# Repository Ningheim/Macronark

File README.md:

# Macronark, a HXH inspired macropad
A macropad inspired by Shalnark's ability in a popular manga called Hunter X Hunter by Yoshihiro Togashi

The "Macronark" is a 12 key macropad with RGB backlit keys. It uses QMK firmware and is upgradable with a 6-pin JST port on the back of the PCB.

## Features:
- Full PLA Shalnark inspired case
- 12 blank DSA keys
- 12 SK6812 MINI-E LEDs for backlighting

## CAD Model:
Everything is fitted together with 6 M3 bolts and heatset inserts. The PCB sits in flush with the case but there is 1 M3 screw hole if you'd like to secure it to your own case.

It's in 2 parts, 1 part for the body and another for the cover.

Made in Onshape
At a later time a seperate PCB will be used to fill the top portion of the case. More RGB LEDs will be used to light up the eye cutouts and a OLED screen will go inside the mouth just as the series depicts it.

## PCB:
The PCB was made in KiCAD, The silkscreen was imported from a Figma image.

#### Schematic

#### PCB

# Finished Product
Once you've printed everything and inserted/soldered all of the components, the result should look like this! (With keycaps of your choice of course 😅)

## Firmware Overview:
This hackpad uses [QMK](https://qmk.fm/) firmware.
- To turn on/off the RGB backlighting, press and hold the top-left key and the bottom-right key together
- All keys act as macros to be assigned to whatever you'd like.

## BOM:
Here's everything you need to make this hackpad
```
-1x Seeed XIAO RP2040
-12x through-hole 1N4148 Diodes
-12x Cherry MX Switches
-12x white blank DSA keycaps
-12x SK6812 MINI-E LEDs
-6x M3x16mm screws
-6x M3x5mx4mm heatset inserts
-1x Case, All 3D Printed
```

Note: Fixed source file issue about the 3mf files. Changed it to steps and stls

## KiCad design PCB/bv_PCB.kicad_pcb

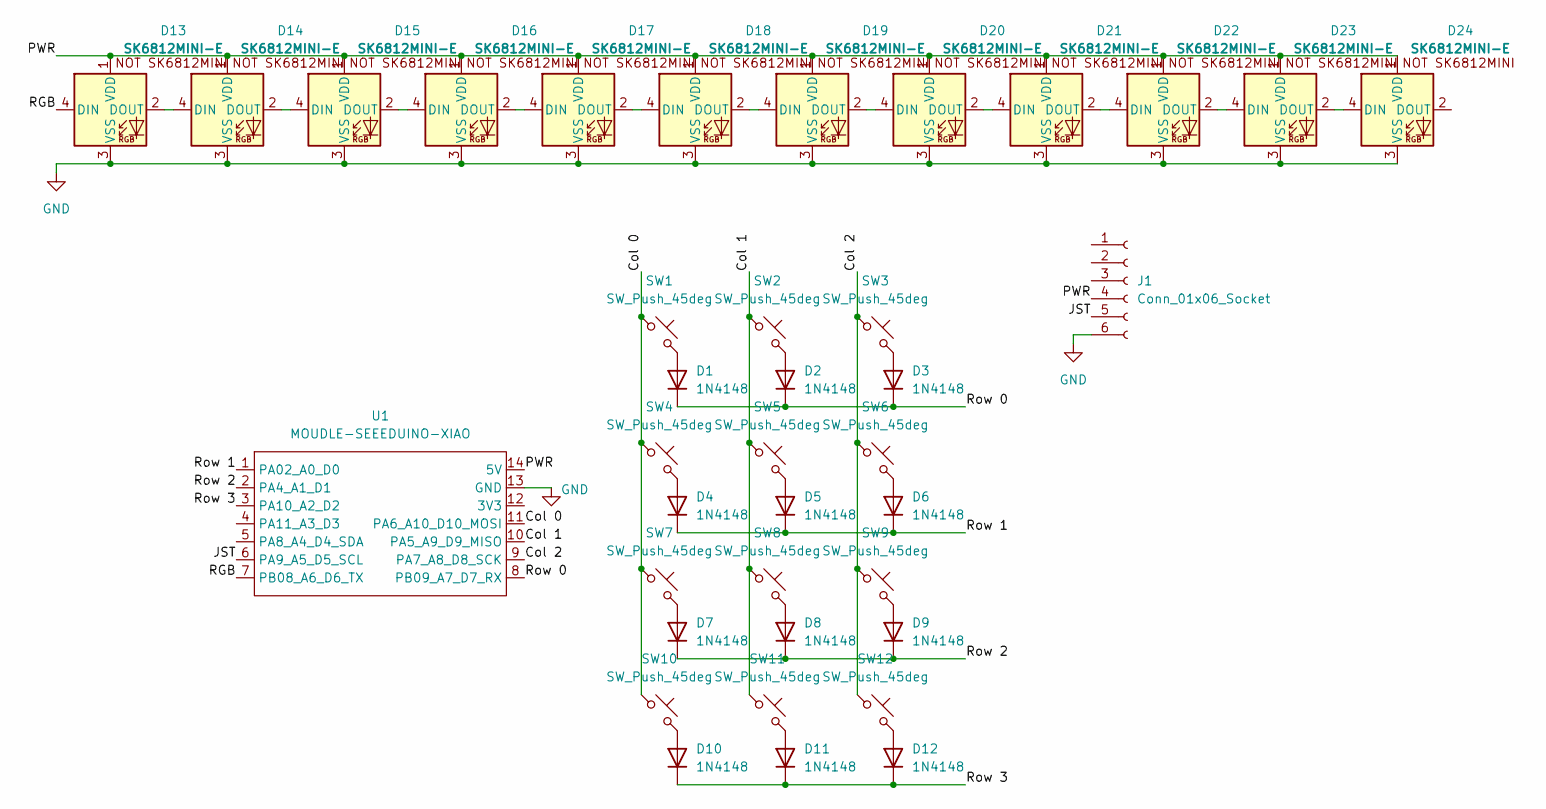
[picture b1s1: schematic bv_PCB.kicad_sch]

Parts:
D1, D2, D3, D4, D5, D6, D7, D8, D9, D10, D11, D12: 1N4148; D_DO-35_SOD27_P7.62mm_Horizontal
D13, D14, D15, D16, D17, D18, D19, D20, D21, D22, D23, D24: SK6812MINI-E; SK6812MINI-E_fixed
J1: Conn_01x06_Socket; JST_PH_S6B-PH-K_1x06_P2.00mm_Horizontal
SW1, SW2, SW3, SW4, SW5, SW6, SW7, SW8, SW9, SW10, SW11, SW12: SW_Push_45deg; SW_Cherry_MX_1.00u_PCB
U1: MOUDLE-SEEEDUINO-XIAO; XIAO-Generic-Hybrid-14P-2.54-21X17.8MM

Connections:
/Col 0: SW1.1, SW4.1, SW7.1, SW10.1, U1.11 (PA6_A10_D10_MOSI)
/Col 1: SW2.1, SW5.1, SW8.1, SW11.1, U1.10 (PA5_A9_D9_MISO)
/Col 2: SW3.1, SW6.1, SW9.1, SW12.1, U1.9 (PA7_A8_D8_SCK)
/JST: J1.5, U1.6 (PA9_A5_D5_SCL)
/PWR: D13.1 (VDD), D14.1 (VDD), D15.1 (VDD), D16.1 (VDD), D17.1 (VDD), D18.1 (VDD), D19.1 (VDD), D20.1 (VDD), D21.1 (VDD), D22.1 (VDD), D23.1 (VDD), D24.1 (VDD), J1.4, U1.14 (5V)
/RGB: D13.4 (DIN), U1.7 (PB08_A6_D6_TX)
/Row 0: D1.1 (K), D2.1 (K), D3.1 (K), U1.8 (PB09_A7_D7_RX)
/Row 1: D4.1 (K), D5.1 (K), D6.1 (K), U1.1 (PA02_A0_D0)
/Row 2: D7.1 (K), D8.1 (K), D9.1 (K), U1.2 (PA4_A1_D1)
/Row 3: D10.1 (K), D11.1 (K), D12.1 (K), U1.3 (PA10_A2_D2)
GND: D13.3 (VSS), D14.3 (VSS), D15.3 (VSS), D16.3 (VSS), D17.3 (VSS), D18.3 (VSS), D19.3 (VSS), D20.3 (VSS), D21.3 (VSS), D22.3 (VSS), D23.3 (VSS), D24.3 (VSS), J1.6, U1.13 (GND)
unnamed: D1.2 (A), SW1.2
unnamed: D2.2 (A), SW2.2
unnamed: D3.2 (A), SW3.2
unnamed: D4.2 (A), SW4.2
unnamed: D5.2 (A), SW5.2
unnamed: D6.2 (A), SW6.2
unnamed: D7.2 (A), SW7.2
unnamed: D8.2 (A), SW8.2
unnamed: D9.2 (A), SW9.2
unnamed: D10.2 (A), SW10.2
unnamed: D11.2 (A), SW11.2
unnamed: D12.2 (A), SW12.2
unnamed: D13.2 (DOUT), D14.4 (DIN)
unnamed: D14.2 (DOUT), D15.4 (DIN)
unnamed: D15.2 (DOUT), D16.4 (DIN)
unnamed: D16.2 (DOUT), D17.4 (DIN)
unnamed: D17.2 (DOUT), D18.4 (DIN)
unnamed: D18.2 (DOUT), D19.4 (DIN)
unnamed: D19.2 (DOUT), D20.4 (DIN)
unnamed: D20.2 (DOUT), D21.4 (DIN)
unnamed: D21.2 (DOUT), D22.4 (DIN)
unnamed: D22.2 (DOUT), D23.4 (DIN)
unnamed: D23.2 (DOUT), D24.4 (DIN)

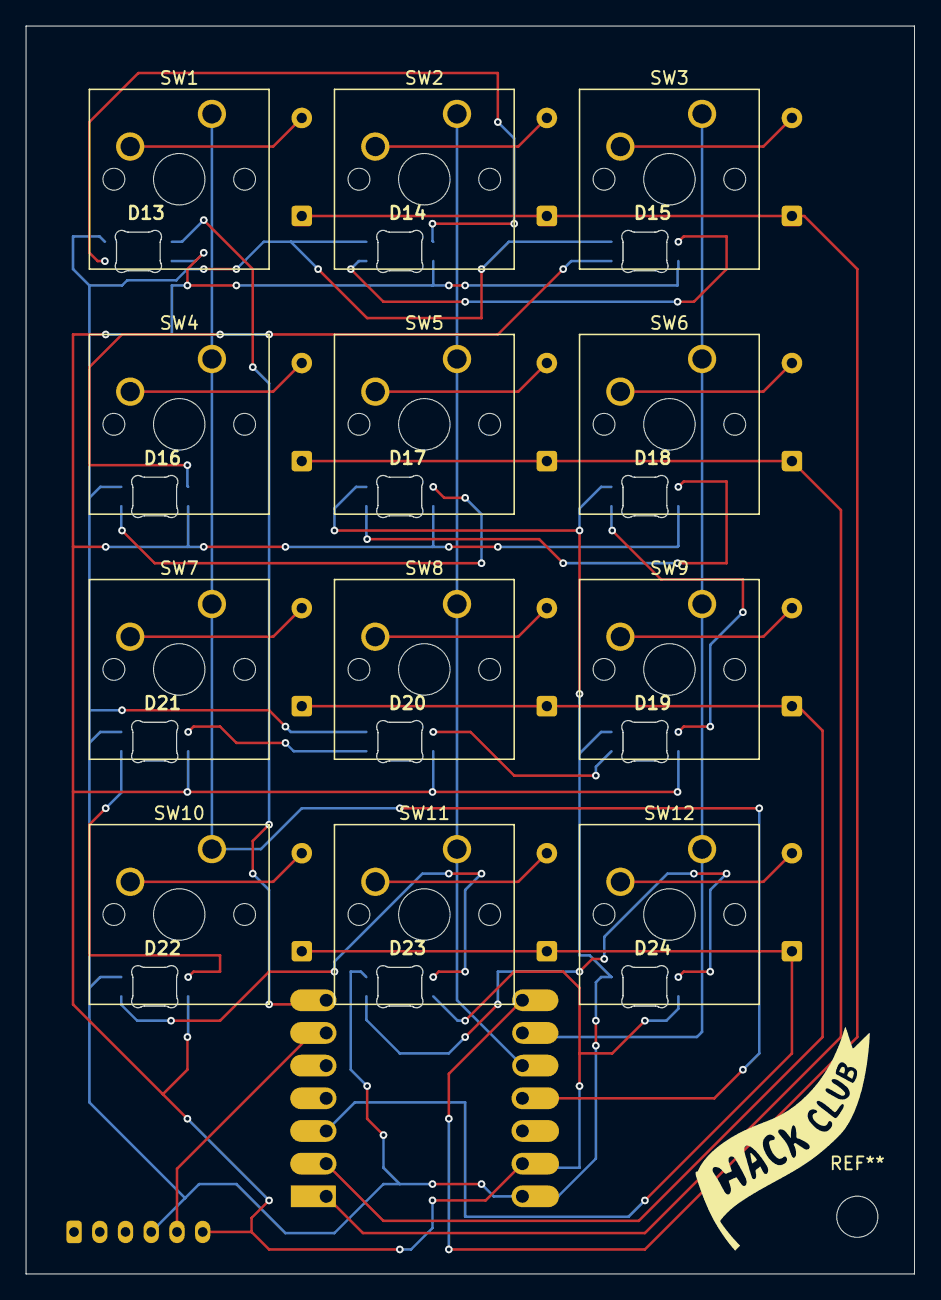
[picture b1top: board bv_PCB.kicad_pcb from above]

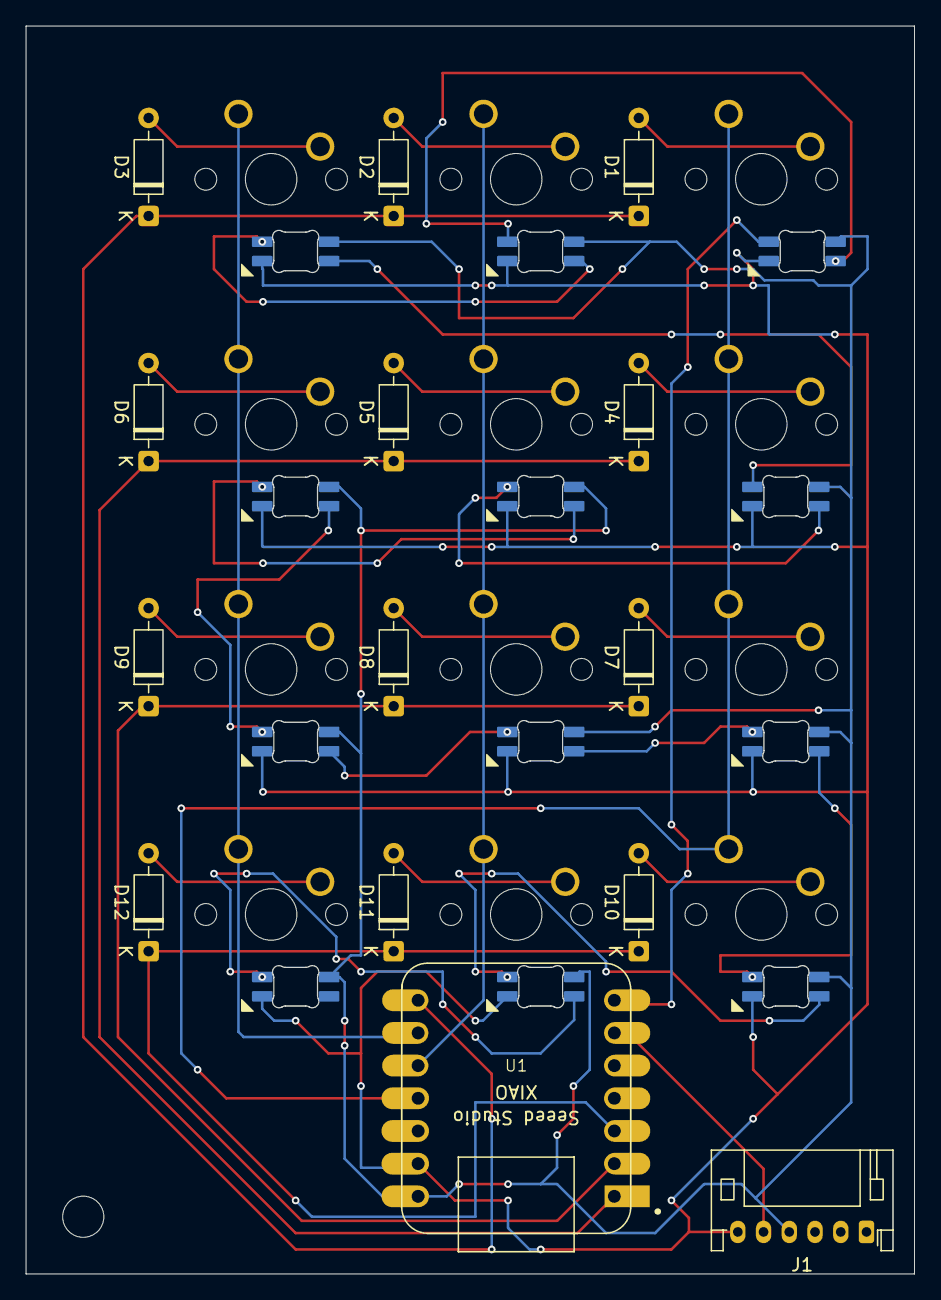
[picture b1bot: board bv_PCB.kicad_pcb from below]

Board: 2 copper layers, 69.1 x 97.0 mm, 38 parts (14 on the bottom side), 34 nets.

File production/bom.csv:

Designator,Footprint,Quantity,Value,LCSC Part #
,462f2333-586c-4cc8-b04d-9995b911b9d8,1,,
"D1, D10, D11, D12, D2, D3, D4, D5, D6, D7, D8, D9",D_DO-35_SOD27_P7.62mm_Horizontal,12,1N4148,
"D13, D14, D15, D16, D17, D18, D19, D20, D21, D22, D23, D24",SK6812MINI-E_fixed,12,SK6812MINI-E,
J1,JST_PH_S6B-PH-K_1x06_P2.00mm_Horizontal,1,Conn_01x06_Socket,
"SW1, SW10, SW11, SW12, SW2, SW3, SW4, SW5, SW6, SW7, SW8, SW9",SW_Cherry_MX_1.00u_PCB,12,SW_Push_45deg,
U1,XIAO-Generic-Hybrid-14P-2.54-21X17.8MM,1,MOUDLE-SEEEDUINO-XIAO,
